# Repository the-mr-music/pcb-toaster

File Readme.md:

# PCB Toaster

> **WARNING:** This project is dealing with 230VAC. You have to take safety preautions and provide proper isolation. Never touch the mains side of the circuit if power is applied. If you are not experienced in high voltage electronics do not attempt to build this circuit. I do take NO WARRANTY or LIABILITY for any damages when building or operating this device.

## Introduction

In my spare time I have been doing quite a lot of PCBs over the years. Starting with SMD sizes of 1206, with increasing circuit complexity I started using smaller and smaller component sizes. From 1206 over 0805, now ending up at 0402 and my first stenciling "adventures". Whilst browsing Instagram, I stumbled upon [Maker Moekoe's Hot Plate Reflow Iron](https://github.com/makermoekoe/Hotplate-Soldering-Iron), from which I grabbed a bit of inspiration for this quite similar project. As I did not have any spare parts lying around and wanted to do something with higher voltages anyway, I decided to build an all-in-one PCB.
(Fun fact - it is not actually a toaster)

## Roadmap

This current project is still work in progress. Be sure to check back later when it's finished.

- [x] Get an iron and disassemble it
- [x] Do all the calculations on the power side
- [x] Component selection
- [x] Design and order the PCB
- [x] Build and test the PCB
- [x] Plan the case and mounting, get materials
- [x] Take a nap
- [x] PCBs arrive 
- [x] Build and wire everything
- [x] Read up theoretical information about reflow soldering and solder paste
- [x] Program a first firmware version (curious if PID regulator will be necessary or a plain two-point regulator is sufficient)
- [ ] Refine the firmware

## PCB Design Notes

### Primary Side

Having only done one pcb incorporating 230 VAC and low voltage (before always used old 5 V phone chargers or other PSUs), but on serparate pcbs, I wanted to opt for an all-on-one pcb design. At LCSC.com I found an affordable print switching PSU ([GTL-POWER-VB02](https://datasheet.lcsc.com/szlcsc/1811211452_GTL-POWER-VB02-T2S03_C335526.pdf)), with an output of 3.3 V at 500 mA, which seemed perfect for the job. Their datasheet (at least the parts I could understand with the help of translator) recommended additional filtering at the output, which has been followed by me. Regarding the primary side, either a simple approach consisting out of a fuse, a varistor and a current limiting resistor or a more EMV saving pre-circuit is possible. As this device is just occasionally in use, the protective circuit is good enough for me.

Regarding the power switch for the iron itself, a BT-138 is used. Primarily because I already had this type of TRIAC already in use together with a MOC3083 and know it's working well together. The resistor values are taken from the MOC's datasheet. Because the SMD resistors have a maximum voltage rating of 250 V, I put two of them in series. All of the tracks carrying the heavy load are approximately five millimeters wide, but run on two layers. As a result a current of in total 10 A is achievable, which is limited by the fuse F1. For ease of layouting, the psu (on fuse F2) and iron are sharing F1. As the iron I use has a cold resistance of 42 Ohms, a 6.3 Ampere fuse is sufficient for F1.

The isolation between any track or plane of different nets is at least five millimeters, depending on the necessity I may also apply a thin layer of spray varnish. To protect against touch, the whole pcb will be mounted behind a sheet of plexiglass.

### Secondary Side

#### Controller

Both controller and peripherals are running at 3.3 V. I decided to connect Earth and GND together (at the cost of more EMV). For someone not wanting this, it is possible to just not fit the resistor R21. In contrast to the primary side, the spacing between Earth and GND is not five, but only three millimeters.

The brain of the circuit is an STM32F103 microcontroller in a small QFN package running at a maximum of 72 MHz. Although way to powerful for the application, it has the advantage to be compatible with the Arduino IDE, so others have an easier time programming their own firmware.
The USB interface of the controller has not been broken out onto the pcb. Any firmware can be flashed by using the SWD interface or the bootloader on the STM32, both accessible through the debug pin socket at the bottom. To activate the bootloader, keep the button pressed and reset the device.
I will be sticking to plain C and the STM32 HAL layer though, more to that in the firmware section.

For temperature measurement I use the MAX6675 thermocouple measurement IC that is connected via SPI to the STM32. The opto triac to turn on the iron is connected to an I/O and has an indicator LED (iron logo) in parallel.

#### User Interaction

The user in total can interact with the device over one push button, one potentiometer, an OLED display and three LEDs.

To set the desired temperature, a potentiometer will be used and read out by the microcontrollers ADC. The AVCC pins have not gotten any additional filtering, as the potentiometer used is just for roughly setting the temperature. Although the STM32 provides a 12 bit ADC, only eight bit are necessary and I will just average a few measurements in the firmware.
For starting or interrupting the heating process the button is used. One can fit a push button directly on the pcb or connect a cable to a button mounted in the plexiglass panel.

To give the user feedback, a small 128x64 px OLED (displays the current temperature, soldering time, etc...) is connected to the STM32 over SPI. Because there were a few spare I/Os left on the controller, I added three more LEDs that can be turned on or off by the firmware.

### PCB Renders

The PCB renders have been created using Greg Davill's KiCAD Script. Order was placed at JLCPCB as I still had other PCBs to be made. First image is the top, second the bot view.

## Simulation

After the PCB has been sent to the fab, I was curious which performance to expect and decided to coarsely model the hot plate in python.
Even though the script is a bit chaotic and is using really coarse values, the result is surprisingly accurate. Those who are interested and have numpy and matplotlib installed can have a look at the Simulation folder.

### PCB Assembly
The soldering itself went quickly, however I can not really recommend the 0402 resistor networks without a stencil. As the components came from LCSC and these were missing in KiCAD, I drew the footprints of the potentiometer, PSU, fuse holders, as well as the OLED and everything fit like a charm.

## Mounting
In order to prevent the terminals from being touched, an acrylic glass will be mounted on top of it. Two cutouts for the potentiometer and button are made.

The plate itself get really hot and should neither damage the base plate (in case of wood) or steal the heat (in case of metal). As solution it is mounted on a piece of FR4, which is in turn screwed to the base plate.

However I still have not decided if I will make the case out of wood or metal. Until the device is fully finished, the PCB is in a plastic box to prevent touching from the bottom and the Iron is mounted on a wooden plate.

## Firmware
With the hardware done, up to the firmware. 

### Libraries used
For easier scheduling and extensibility I chose to deploy a freeRTOS on the device in conjunction with the STM32 HAL libraries. Then the really good u8g2 library by Oli Kraus for controlling the OLED and finally an own implementation of Brett Beauregard's well working PID controller.

### Iron Power Control

Wave packet control. Prescaler of 8000 @ 64 MHz core clock. Timer in PWM mode with 8000 period -> 1 second. One half wave is 10 ms. error is x

Simulation results show a maximum temperature increase per second of around 2,5 °C. This is below the allowed 3 °C increase per second. When heating the iron with maximum power, it is

As the power of the plate is not high enough support the accurate temperature profile, I will try to take a different approach. At first preheat with maximum heat to 100 °C, at which point the flux starts activating. After the flux is active, the whole soldering process should be completed in three minutes. A PID regulator will then take care of regulating it to the peak temperature.

### Tasks
The first task deals with reading out and preprocessing the thermocouple temperature. The MAX6675 in worst case needs 225ms for one conversion. With SPI at 4 MHz one can achieve four temperature readings in one second. If the value passes the sanity check, it is added to a ringbuffer. This way always the last four temperature readings get averaged providing a stable temperature reading once per second, matching our PID regulator's calculation interval.

The second task is 

control task. Oled, logging and 

pid task. PID regulator based on brett beauregards code.

Currently only one temperature curve is programmed for the Chipquik TS391AX50 (Sn63/PB37, TAL@183 °C). The potentiometer is 

<p>&copy; T. Music 2019<br/>This work is licensed under CC BY-SA 4.0 (https://creativecommons.org/licenses/by-sa/4.0/legalcode)</p>

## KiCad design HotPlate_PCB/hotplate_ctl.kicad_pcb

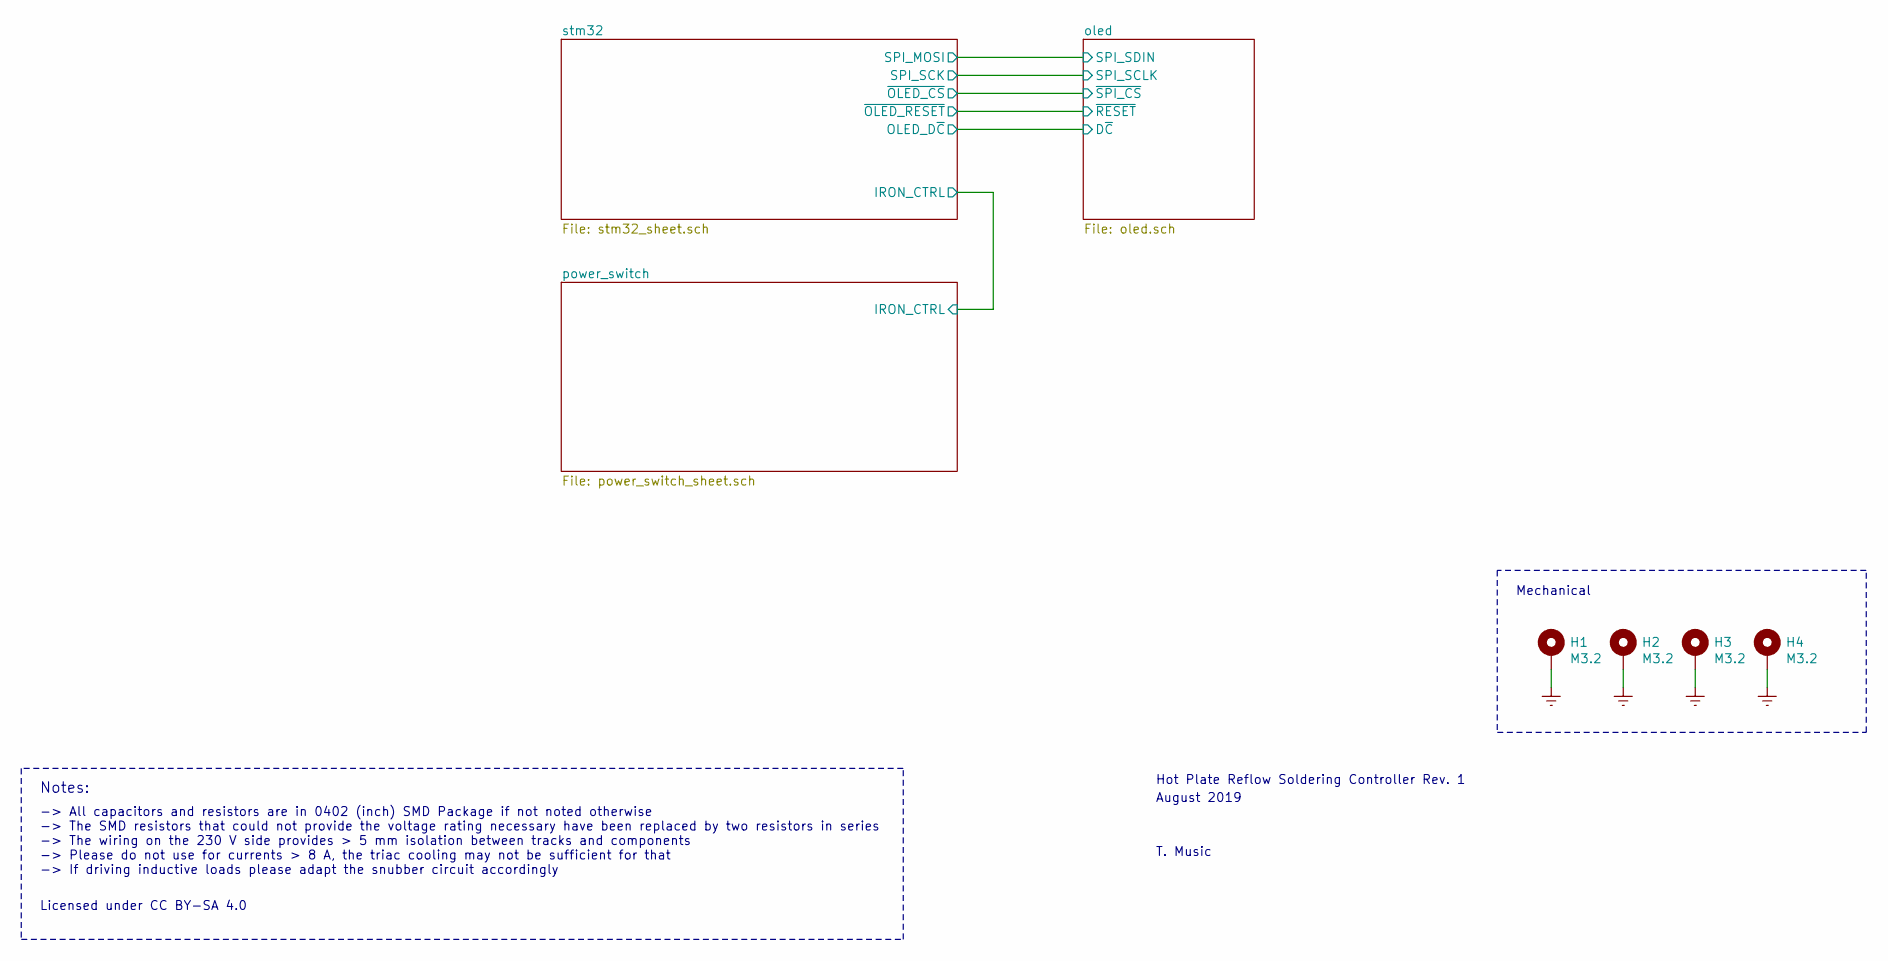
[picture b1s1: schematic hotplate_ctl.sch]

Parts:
H1, H2, H3, H4: M3.2; MountingHole_3.2mm_M3_DIN965_Pad

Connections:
Earth: H1.1, H2.1, H3.1, H4.1; also elsewhere on the board

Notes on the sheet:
Hot Plate Reflow Soldering Controller Rev. 1
August 2019
T. Music
-> All capacitors and resistors are in 0402 (inch) SMD Package if not noted otherwise -> The SMD resistors that could not provide the voltage rating necessary have been replaced by two resistors in series -> The wiring on the 230 V side provides > 5 mm isolation between tracks and components -> Ple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
Notes:
Licensed under CC BY-SA 4.0
Mechanical

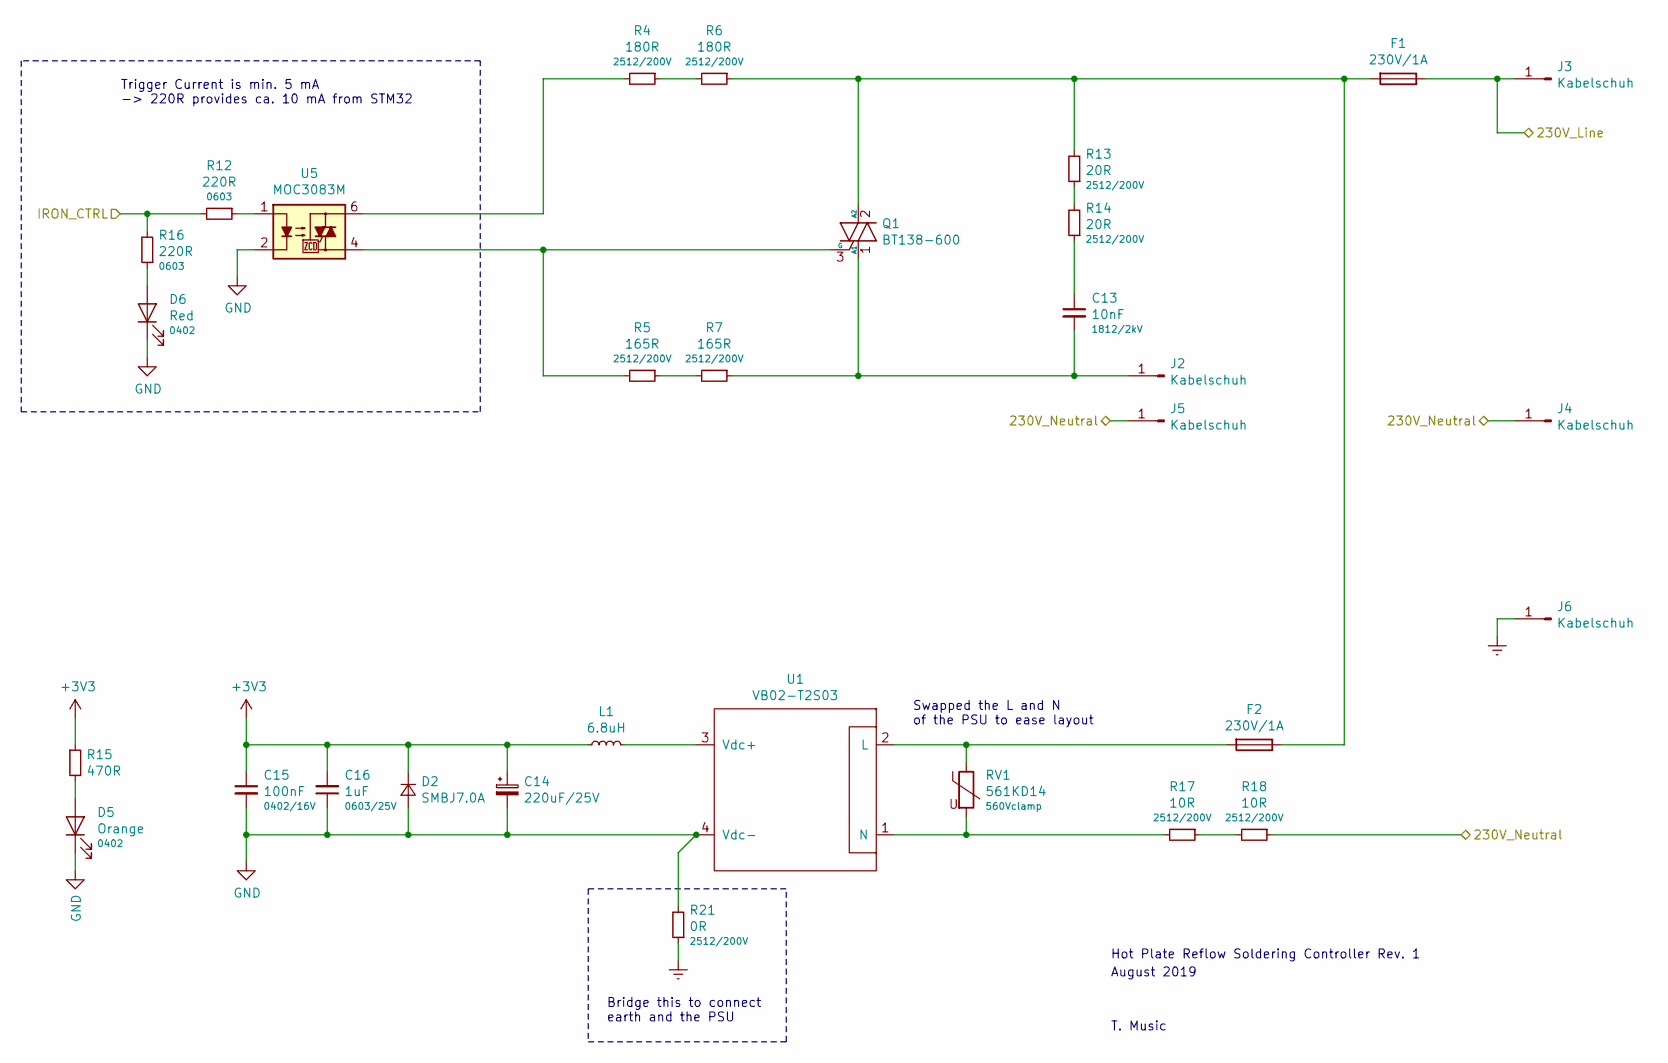
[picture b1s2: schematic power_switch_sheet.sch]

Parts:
C13: 10nF; C_1812_4532Metric
C14: 220uF/25V; CP_Elec_8x10.5
C15: 100nF; C_0402_1005Metric; Rating 0402/16V
C16: 1uF; C_0603_1608Metric; Rating 0603/25V; LCSC C23630
D2: SMBJ7.0A; D_SMB
D5: Orange; LED_0402_1005Metric; Rating 0402
D6: Red; LED_0402_1005Metric; Rating 0402
F1, F2: 230V/1A; XC-Elec-C3130
J2, J3, J4, J5, J6: Kabelschuh; kabelschuh_horizontal_8x19mm
L1: 6.8uH; SM4532
Q1: BT138-600; TO-263-2
R4, R6: 180R; R_2512_6332Metric; Rating 2512/200V
R5, R7: 165R; R_2512_6332Metric; Rating 2512/200V
R12, R16: 220R; R_0603_1608Metric; Rating 0603
R13, R14: 20R; R_2512_6332Metric; Rating 2512/200V
R15: 470R; R_0402_1005Metric
R17, R18: 10R; R_2512_6332Metric; Rating 2512/200V
R21: 0R; R_2512_6332Metric; Rating 2512/200V
RV1: 561KD14; RV_Disc_D15.5mm_W5mm_P7.5mm; Rating 560Vclamp
U1: VB02-T2S03; VB02-T2Sxx
U5: MOC3083M; DIP-6_W8.89mm_SMDSocket_LongPads

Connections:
+3V3: C14.1, C15.1, C16.2, D2.1 (K), L1.1, R15.1; also elsewhere on the board
/power_switch/230V_Line: F1.1, J3.1
/power_switch/230V_Neutral: J4.1, J5.1, R18.1
/power_switch/IRON_CTRL: R12.2, R16.2; also elsewhere on the board
Earth: J6.1, R21.1; also elsewhere on the board
GND: C14.2, C15.2, C16.1, D2.2 (A), D5.1 (K), D6.1 (K), R21.2, U1.4 (Vdc-), U5.2; also elsewhere on the board
unnamed: C13.1, R14.1
unnamed: C13.2, J2.1, Q1.1 (A1), R7.1
unnamed: D5.2 (A), R15.2
unnamed: D6.2 (A), R16.1
unnamed: F1.2, F2.1, Q1.2 (A2), R6.1, R13.2
unnamed: F2.2, RV1.1, U1.2 (L)
unnamed: L1.2, U1.3 (Vdc+)
unnamed: Q1.3 (G), R5.2, U5.4
unnamed: R4.1, R6.2
unnamed: R4.2, U5.6
unnamed: R5.1, R7.2
unnamed: R12.1, U5.1
unnamed: R13.1, R14.2
unnamed: R17.1, R18.2
unnamed: R17.2, RV1.2, U1.1 (N)

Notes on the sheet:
Trigger Current is min. 5 mA -> 220R provides ca. 10 mA from STM32
Bridge this to connect earth and the PSU
Swapped the L and N of the PSU to ease layout
Hot Plate Reflow Soldering Controller Rev. 1
August 2019
T. Music

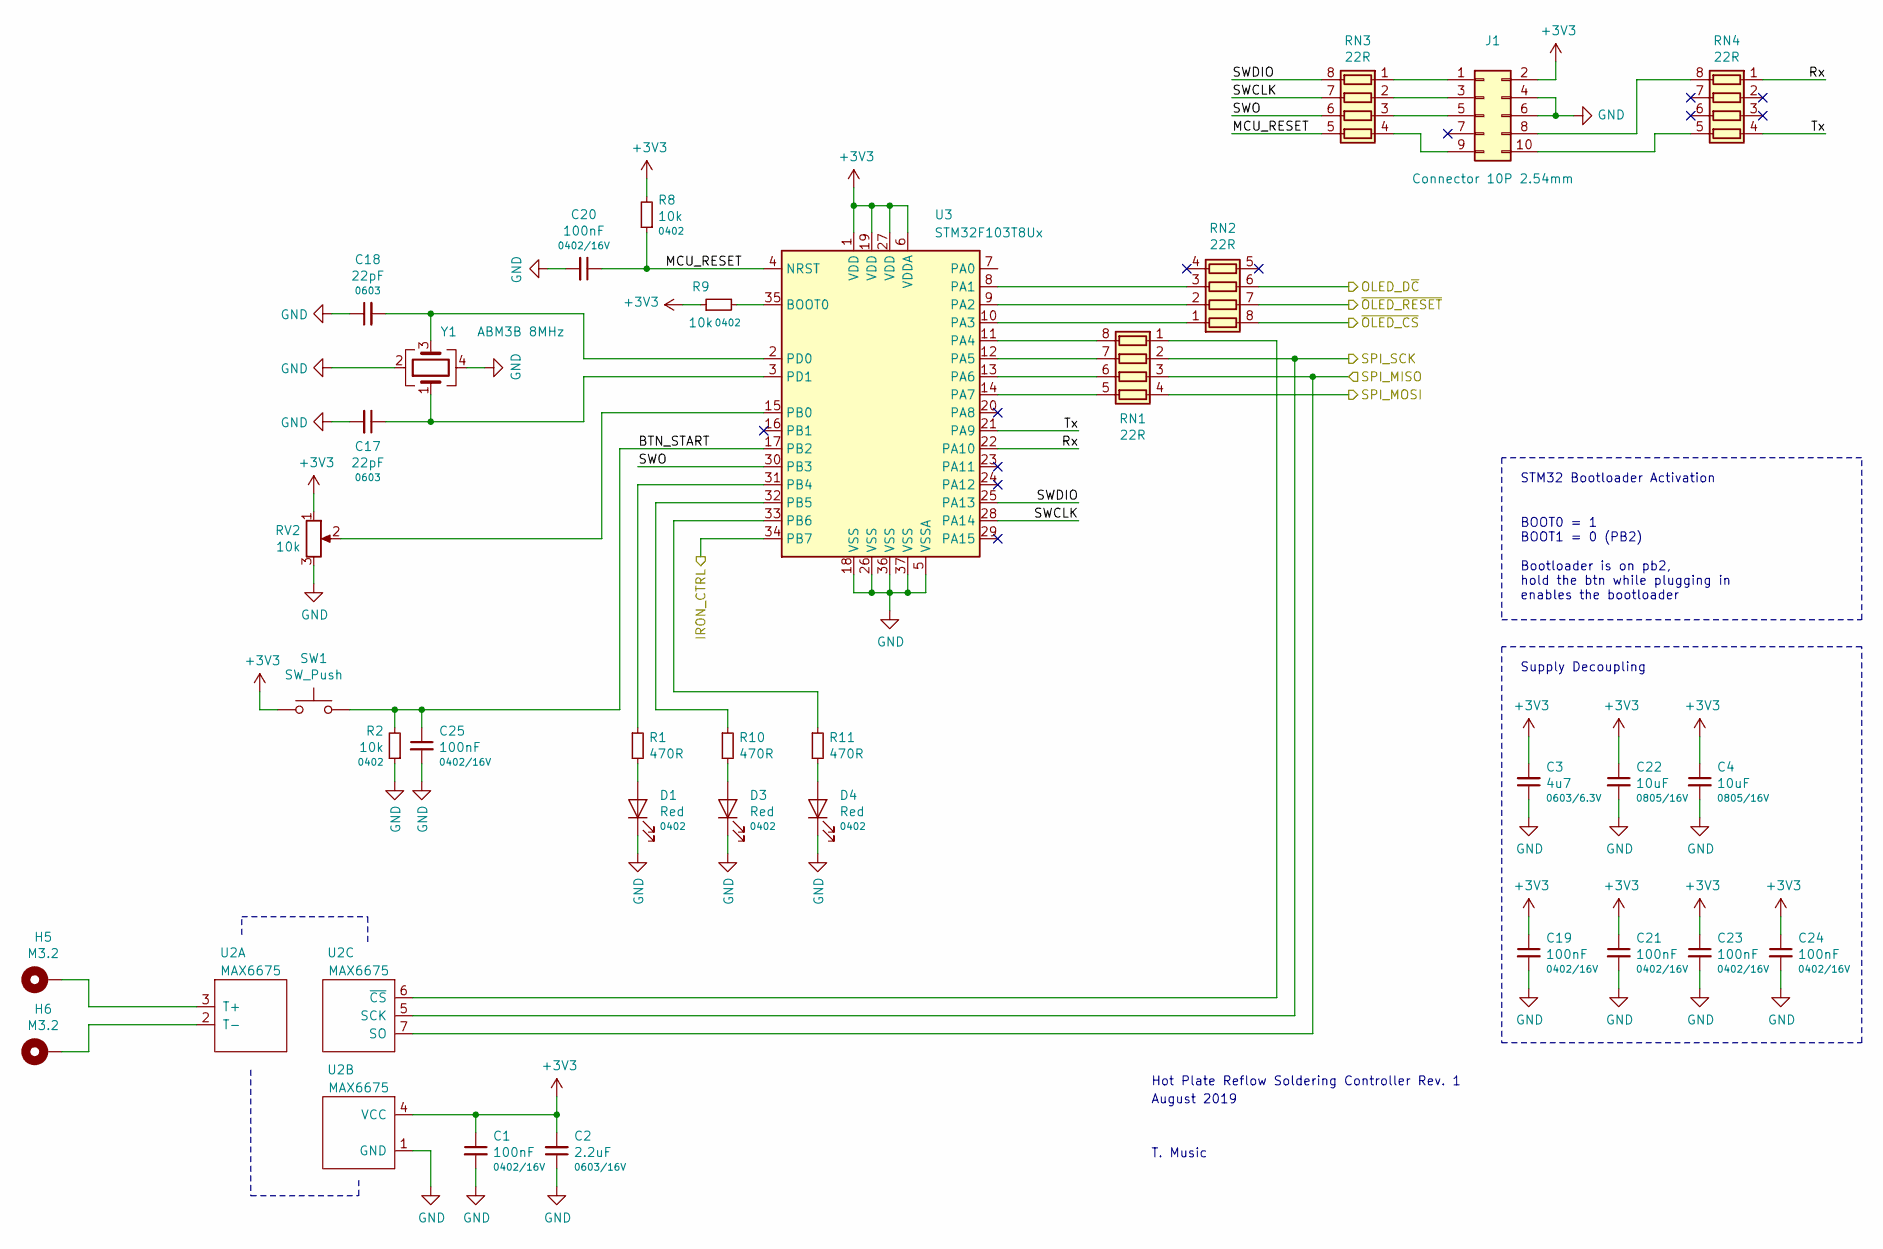
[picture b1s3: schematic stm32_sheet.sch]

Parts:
C1, C19, C20, C21, C23, C24, C25: 100nF; C_0402_1005Metric; Rating 0402/16V
C2: 2.2uF; C_0603_1608Metric; Rating 0603/16V; LCSC C23630
C3: 4u7; C_0603_1608Metric; Rating 0603/6.3V
C4, C22: 10uF; C_0805_2012Metric; Rating 0805/16V
C17, C18: 22pF; C_0603_1608Metric; Rating 0603
D1, D3, D4: Red; LED_0402_1005Metric; Rating 0402
H5, H6: M3.2; MountingHole_3.2mm_M3_DIN965_Pad
J1: Connector 10P 2.54mm; PinSocket_2x05_P2.54mm_Horizontal
R1, R10, R11: 470R; R_0402_1005Metric
R2, R8, R9: 10k; R_0402_1005Metric; Rating 0402
RN1, RN2, RN3, RN4: 22R; R_Array_Convex_4x0402
RV2: 10k; Potentiometer_Hole_10mm
SW1: SW_Push; SW_SPST_B3S-1000
U2: MAX6675; SO-8_3.9x4.9mm_P1.27mm
U3: STM32F103T8Ux; QFN-36-1EP_6x6mm_P0.5mm_EP4.1x4.1mm
Y1: ABM3B 8MHz; Crystal_SMD_Abracon_ABM3B-4Pin_5.0x3.2mm

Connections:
+3V3: C1.1, C2.2, C3.2, C4.1, C19.1, C21.1, C22.1, C23.1, C24.1, J1.2, R8.2, R9.1, RV2.1, SW1.1, U2.4 (VCC), U3.1 (VDD), U3.6 (VDDA), U3.19 (VDD), U3.27 (VDD); also elsewhere on the board
/oled/D~C: RN2.6 (R3.2); also elsewhere on the board
/power_switch/IRON_CTRL: U3.34 (PB7); also elsewhere on the board
/stm32/BTN_START: C25.1, R2.2, SW1.2, U3.17 (PB2)
/stm32/MCU_RESET: C20.1, R8.1, RN3.5 (R4.2), U3.4 (NRST)
/stm32/Rx: RN4.1 (R1.1), U3.22 (PA10)
/stm32/SPI_MISO: RN1.3 (R3.1), U2.7 (SO)
/stm32/SPI_MOSI: RN1.4 (R4.1); also elsewhere on the board
/stm32/SPI_SCK: RN1.2 (R2.1), U2.5 (SCK); also elsewhere on the board
/stm32/SWCLK: RN3.7 (R2.2), U3.28 (PA14)
/stm32/SWDIO: RN3.8 (R1.2), U3.25 (PA13)
/stm32/SWO: RN3.6 (R3.2), U3.30 (PB3)
/stm32/Tx: RN4.4 (R4.1), U3.21 (PA9)
/stm32/~OLED_CS: RN2.8 (R1.2); also elsewhere on the board
/stm32/~OLED_RESET: RN2.7 (R2.2); also elsewhere on the board
GND: C1.2, C2.1, C3.1, C4.2, C17.2, C18.1, C19.2, C20.2, C21.2, C22.2, C23.2, C24.2, C25.2, D1.1 (K), D3.1 (K), D4.1 (K), J1.4, J1.6, R2.1, RV2.3, U2.1 (GND), U3.5 (VSSA), U3.18 (VSS), U3.26 (VSS), U3.36 (VSS), U3.37 (VSS), Y1.2, Y1.4; also elsewhere on the board
unnamed: C17.1, U3.3 (PD1), Y1.1
unnamed: C18.2, U3.2 (PD0), Y1.3
unnamed: D1.2 (A), R1.2
unnamed: D3.2 (A), R10.2
unnamed: D4.2 (A), R11.2
unnamed: H5.1, U2.3 (T+)
unnamed: H6.1, U2.2 (T-)
unnamed: J1.1, RN3.1 (R1.1)
unnamed: J1.3, RN3.2 (R2.1)
unnamed: J1.5, RN3.3 (R3.1)
unnamed: J1.8, RN4.8 (R1.2)
unnamed: J1.9, RN3.4 (R4.1)
unnamed: J1.10, RN4.5 (R4.2)
unnamed: R1.1, U3.31 (PB4)
unnamed: R9.2, U3.35 (BOOT0)
unnamed: R10.1, U3.32 (PB5)
unnamed: R11.1, U3.33 (PB6)
unnamed: RN1.1 (R1.1), U2.6 (~CS)
unnamed: RN1.5 (R4.2), U3.14 (PA7)
unnamed: RN1.6 (R3.2), U3.13 (PA6)
unnamed: RN1.7 (R2.2), U3.12 (PA5)
unnamed: RN1.8 (R1.2), U3.11 (PA4)
unnamed: RN2.1 (R1.1), U3.10 (PA3)
unnamed: RN2.2 (R2.1), U3.9 (PA2)
unnamed: RN2.3 (R3.1), U3.8 (PA1)
unnamed: RV2.2, U3.15 (PB0)

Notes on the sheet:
BOOT0 = 1 BOOT1 = 0 (PB2) Bootloader is on pb2, hold the btn while plugging in enables the bootloader
Supply Decoupling
STM32 Bootloader Activation
Hot Plate Reflow Soldering Controller Rev. 1
August 2019
T. Music

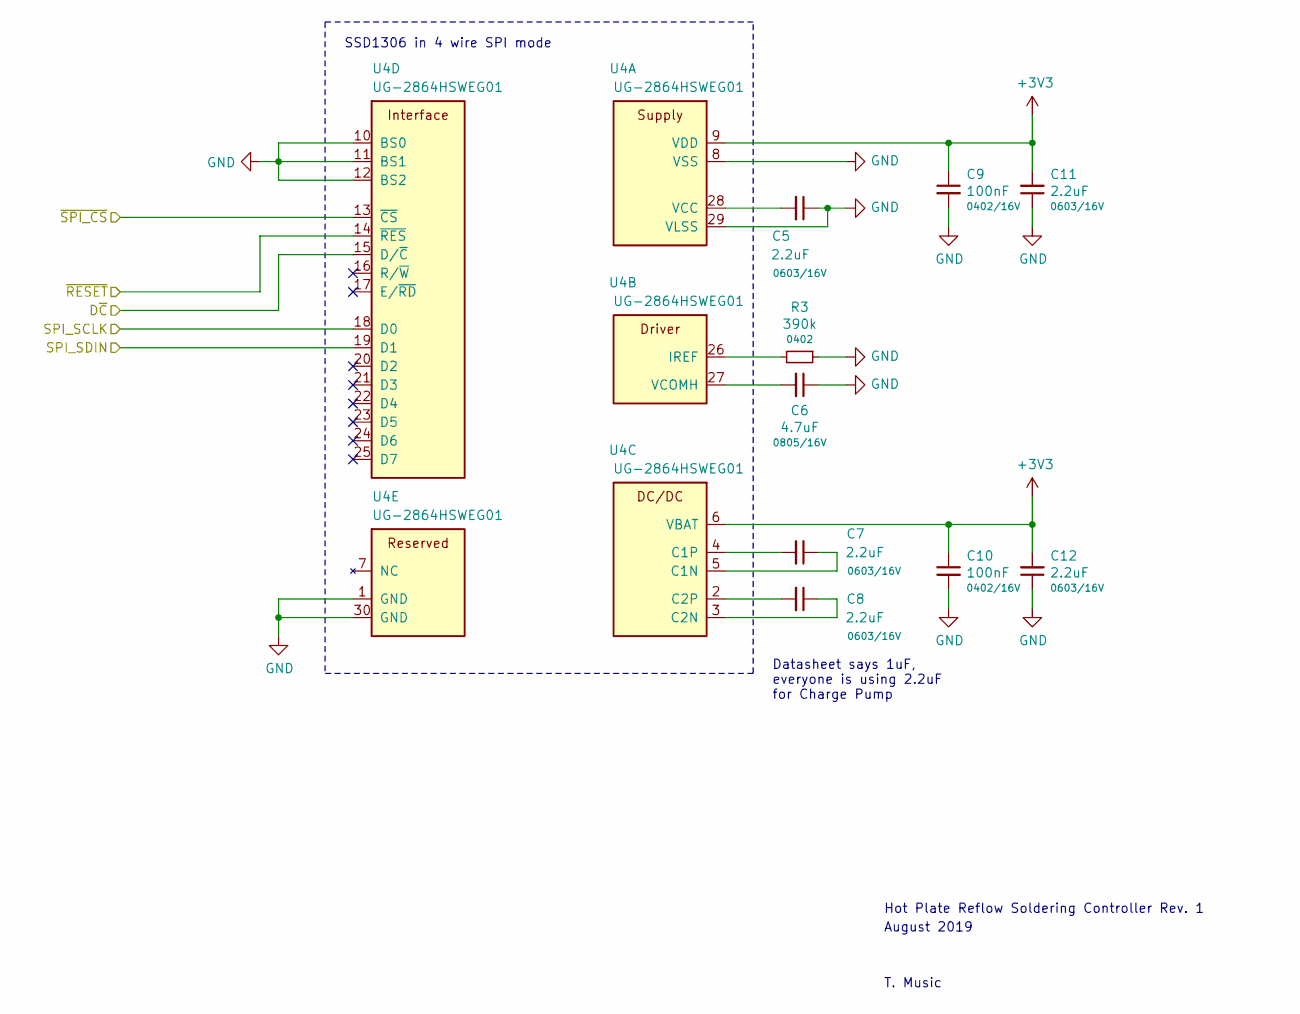
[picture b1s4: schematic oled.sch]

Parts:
C10, C31: 100nF; C_0402_1005Metric; Rating 0402/16V
C11, C12, C27, C29, C30: 2.2uF; C_0603_1608Metric; Rating 0603/16V; LCSC C23630
C28: 4.7uF; C_0805_2012Metric; Rating 0805/16V
R41: 390k; R_0402_1005Metric; Rating 0402
U9: UG-2864HSWEG01

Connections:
+3V3: C10.1, C11.2, C12.2; also elsewhere on the board
GND: C10.2, C11.1, C12.1; also elsewhere on the board

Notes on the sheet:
SSD1306 in 4 wire SPI mode
Datasheet says 1uF, everyone is using 2.2uF for Charge Pump
Hot Plate Reflow Soldering Controller Rev. 1
August 2019
T. Music

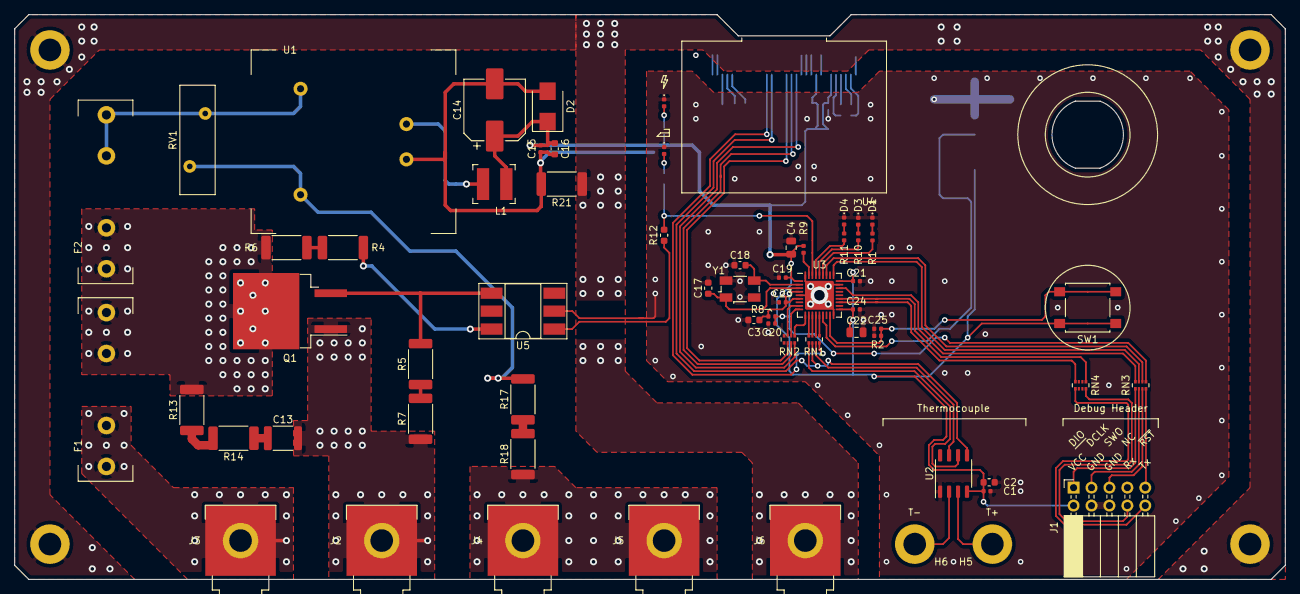
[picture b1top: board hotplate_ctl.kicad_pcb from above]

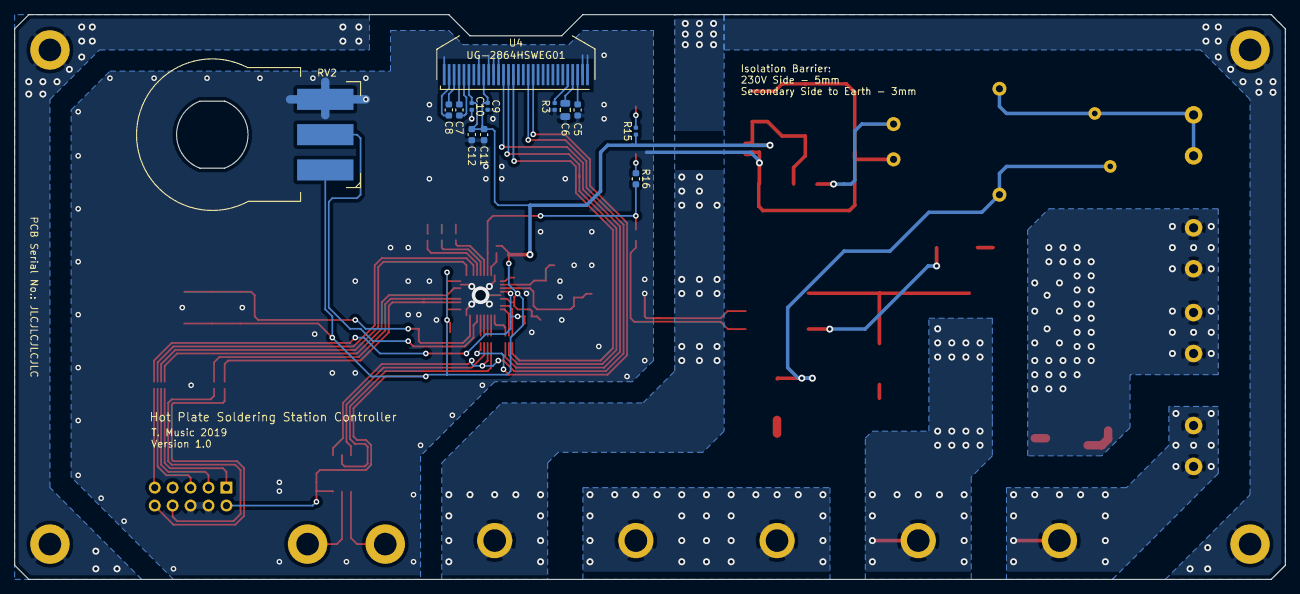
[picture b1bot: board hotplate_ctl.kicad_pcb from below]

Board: 2 copper layers, 180.0 x 80.0 mm, 79 parts (12 on the bottom side), 67 nets.

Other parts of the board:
C5, C7, C8: 2.2uF; C_0603_1608Metric
C6: 4.7uF; C_0805_2012Metric
C9: 100nF; C_0402_1005Metric
R3: 390k; R_0402_1005Metric
U4: UG-2864HSWEG01

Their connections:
+3V3: C9.1, U4.6, U4.9; also elsewhere on the board
/oled/D~C: U4.15; also elsewhere on the board
/stm32/SPI_MOSI: U4.19; also elsewhere on the board
/stm32/SPI_SCK: U4.18; also elsewhere on the board
/stm32/~OLED_CS: U4.13; also elsewhere on the board
/stm32/~OLED_RESET: U4.14; also elsewhere on the board
GND: C5.1, C6.1, C9.2, R3.1, U4.1, U4.8, U4.10, U4.11, U4.12, U4.29, U4.30; also elsewhere on the board
unnamed: C5.2, U4.28
unnamed: C6.2, U4.27
unnamed: C7.1, U4.5
unnamed: C7.2, U4.4
unnamed: C8.1, U4.3
unnamed: C8.2, U4.2
unnamed: R3.2, U4.26

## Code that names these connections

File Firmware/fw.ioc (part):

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Mcu.Name=STM32F103T(8-B)Ux
Mcu.Package=VFQFPN36
Mcu.UserName=STM32F103T8Ux
PA1.GPIOParameters=GPIO_Label
PA1.GPIO_Label=OLED_DC
PA1.Signal=GPIO_Output
PA10.Mode=Asynchronous
PA10.Signal=USART1_RX
PA13.Mode=Trace_Asynchronous_SW
PA13.Signal=SYS_JTMS-SWDIO
PA14.Mode=Trace_Asynchronous_SW
PA14.Signal=SYS_JTCK-SWCLK
PA2.GPIOParameters=GPIO_Label
PA2.GPIO_Label=OLED_RESET
PA2.Signal=GPIO_Output
PA3.GPIOParameters=GPIO_Label
PA3.GPIO_Label=OLED_CS
PA3.Signal=GPIO_Output
PA4.GPIOParameters=GPIO_Label
PA4.GPIO_Label=TC_CS
PA4.Signal=GPIO_Output
PA5.Mode=Full_Duplex_Master
PA5.Signal=SPI1_SCK
PA6.Mode=Full_Duplex_Master
PA6.Signal=SPI1_MISO
PA7.Mode=Full_Duplex_Master
PA7.Signal=SPI1_MOSI
PA9.Mode=Asynchronous
PA9.Signal=USART1_TX
PB0.GPIOParameters=GPIO_Label
PB0.GPIO_Label=POTI_ADC
PB0.Signal=ADCx_IN8
PB2.GPIOParameters=GPIO_Label
PB2.GPIO_Label=BTN_START
PB2.Signal=GPIO_Input
PB3.Mode=Trace_Asynchronous_SW
PB3.Signal=SYS_JTDO-TRACESWO
PB4.GPIOParameters=GPIO_Label
PB4.GPIO_Label=LED1
PB4.Signal=GPIO_Output
PB5.GPIOParameters=GPIO_Label
PB5.GPIO_Label=LED2
PB5.Signal=GPIO_Output
PB6.GPIOParameters=GPIO_Label
PB6.GPIO_Label=LED3
PB6.Signal=GPIO_Output
PB7.GPIOParameters=GPIO_Speed,GPIO_Label
PB7.GPIO_Label=IRON_CTL
PB7.GPIO_Speed=GPIO_SPEED_FREQ_LOW
PB7.Signal=S_TIM4_CH2
PD0-OSC_IN.Mode=HSE-External-Oscillator
PD0-OSC_IN.Signal=RCC_OSC_IN
PD1-OSC_OUT.Mode=HSE-External-Oscillator
PD1-OSC_OUT.Signal=RCC_OSC_OUT
RCC.SYSCLKFreq_VALUE=64000000
RCC.SYSCLKSource=RCC_SYSCLKSOURCE_PLLCLK
board=custom

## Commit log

2019-08-30 First commit. Added images, preliminary readme, gitignore and license
2019-08-30 Added KiCAD files of rev1
2019-08-30 Updated renders
2019-08-30 Changed Readme
2019-08-30 Added firmware and few datasheets
2019-09-12 Firmware WIP
2019-09-14 Improved logging script to plot
2019-09-15 SW WIP, regulator does not respond well to predefined curve from table
2019-09-19 Coarse simulation of the hot plate
2019-09-19 RTOS Sources will not be in git, added placeholder
2019-09-19 Updated Firmware, code still needs cleanup and a sleeker UI
2019-09-19 Added interactive BOM
2019-09-19 Added Makefile and STM32CubeMX configs
2019-09-19 Made PCB view prettier
2019-09-19 Added python logging and plotting script
2019-09-19 Drivers from ST and U8G2 lib are not in the repo
2019-09-19 Added temperature logs to gitignore
2019-09-28 Adding more to the documentation

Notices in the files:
Readme.md:
License: CC BY-SA 4.0
